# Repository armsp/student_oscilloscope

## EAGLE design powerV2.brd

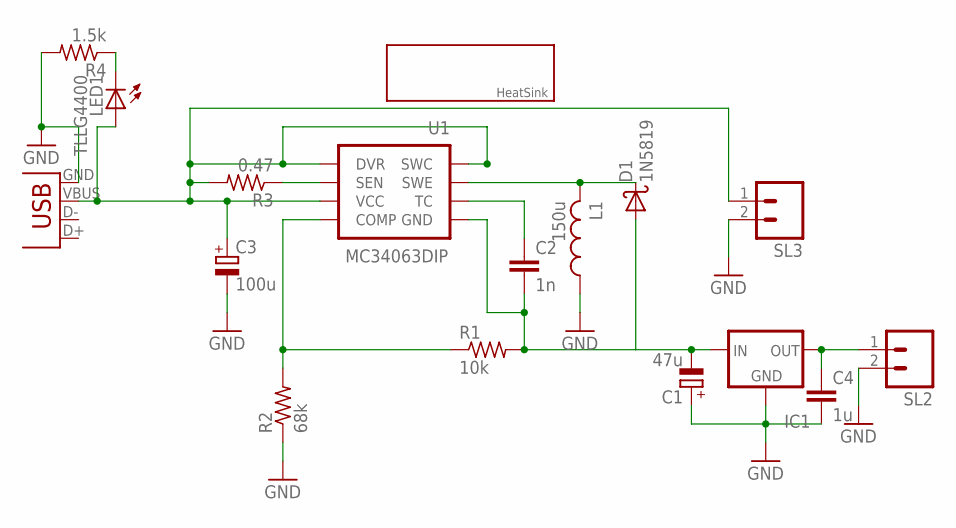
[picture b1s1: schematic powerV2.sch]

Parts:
C1: 47u; E2,5-7
C2: 1n; C025-024X044
C3: 100u; E2,5-7
C4: 1u; C025-024X044
D1: 1N5819; DO41-10
IC1: 79XXS
L1: 150u; 0204/7
LED1: TLLG4400; LED3MM
R1: 10k; 0204/7
R2: 68k; 0204/7
R3: 0.47; P0613/15
R4: 1.5k; 0204/7
SL2, SL3: M02; 02P
U1: MC34063DIP; DIP-08
U$1: HEATSINKMEDIUM; HEATSINK-MED
X1: USBSMD; USB-MINIB

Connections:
GND: C1.+, C3.-, C4.2, IC1.GND, L1.1, R2.1, R4.2, SL2.2, SL3.2, X1.GND
unnamed: R3.1, U1.7 (SEN)
unnamed: C3.+, LED1.A, R3.2, SL3.1, U1.1 (SWC), U1.6 (VCC), U1.8 (DVR), X1.VBUS
unnamed: C4.1, IC1.OUT, SL2.1
unnamed: C1.-, C2.2, D1.A, IC1.IN, R1.2, U1.4 (GND)
unnamed: R1.1, R2.2, U1.5 (COMP)
unnamed: D1.C, L1.2, U1.2 (SWE)
unnamed: C2.1, U1.3 (TC)
unnamed: LED1.K (C), R4.1

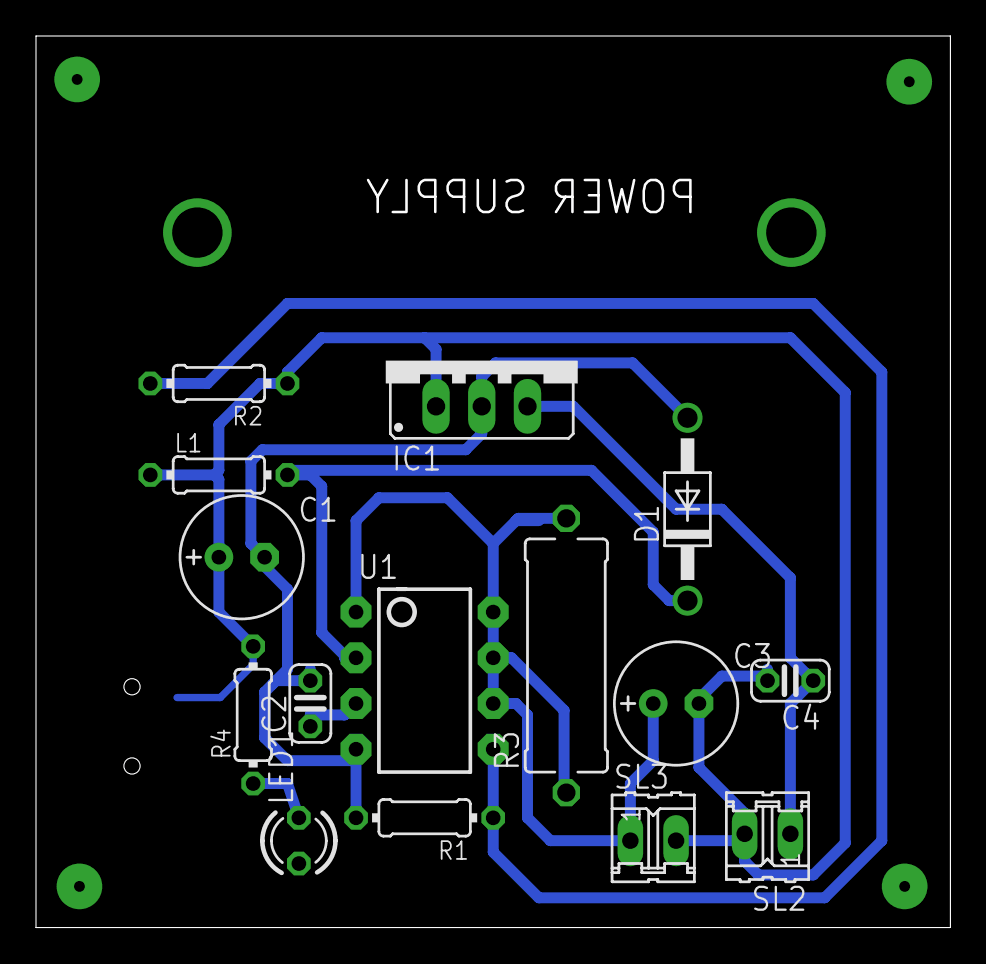
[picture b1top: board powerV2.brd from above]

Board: 2 copper layers, 50.8 x 49.5 mm, 17 parts (1 on the bottom side), 9 nets.

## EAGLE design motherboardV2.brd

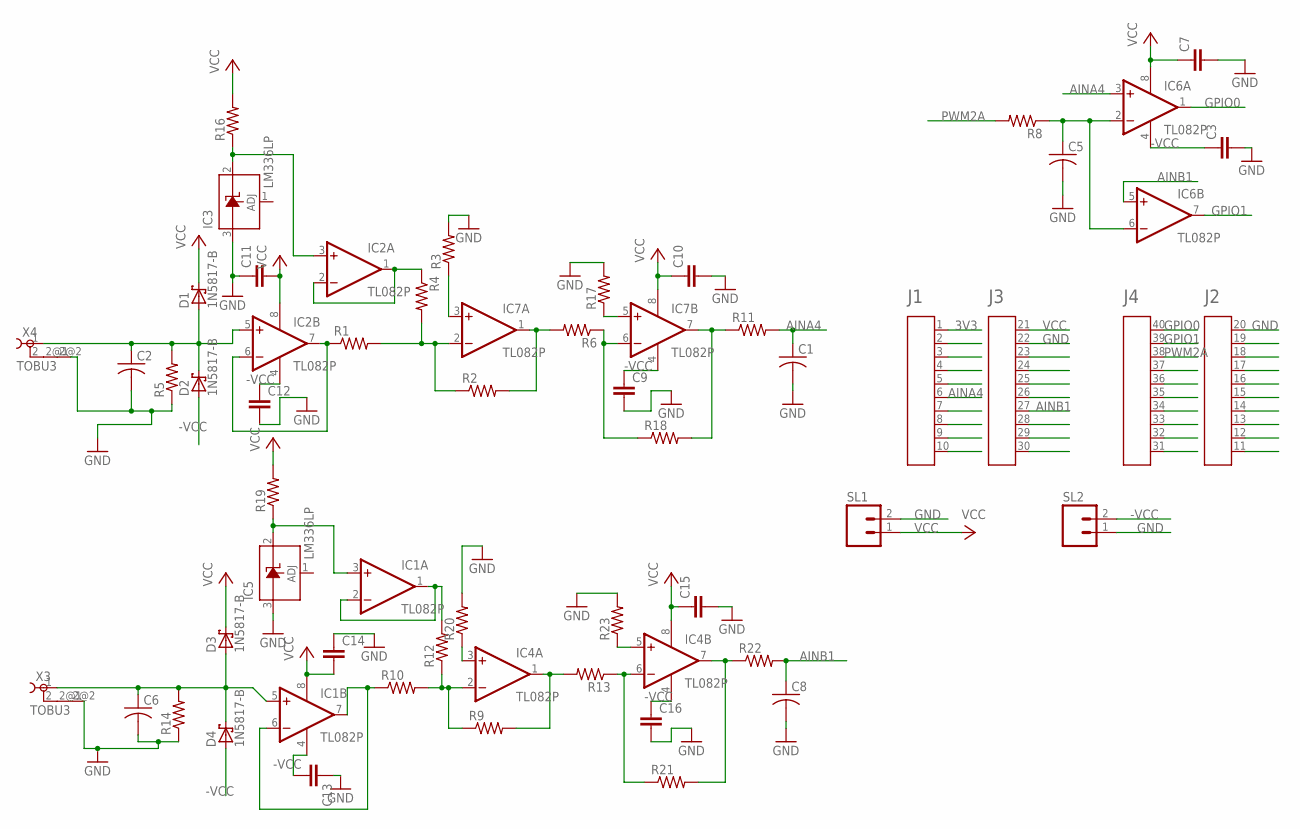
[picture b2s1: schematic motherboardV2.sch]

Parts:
A1: HEADER4X10-BOOSTERPACK; 4X10-BOOSTERPACK
C1, C2, C5, C6, C8: C-US025-025X050; C025-025X050
C3, C7, C9, C10, C11, C13, C14, C15, C16: C-EU025-025X050; C025-025X050
C12: C-EU025-030X050; C025-030X050
D1, D2, D3, D4: 1N5817-B; DO41-7.6
IC1, IC2, IC4, IC6, IC7: TL082P; DIL08
IC3, IC5: LM336LP; TO92
R1, R2, R3, R4, R5, R6, R8, R9, R10, R11, R12, R13, R14, R16, R17, R18, R19, R20, R21, R22, R23: R-US_0207/7; 0207/7
SL1, SL2: M02; 02P
X3, X4: TOBU3

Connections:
3V3: A1.1
-VCC: C3.1, C9.1, C12.1, C13.2, C16.1, D2.A, D4.A, IC1.4 (V-), IC2.4 (V-), IC4.4 (V-), IC6.4 (V-), IC7.4 (V-), SL2.2
AINA4: A1.6, C1.1, IC6.3 (+IN), R11.2
AINB1: A1.27, C8.1, IC6.5 (+IN), R22.2
GND: A1.20, A1.22, C1.2, C2.2, C3.2, C5.2, C6.2, C7.2, C8.2, C9.2, C10.2, C11.1, C12.2, C13.1, C14.1, C15.2, C16.2, IC3.3 (A), IC5.3 (A), R3.2, R5.1, R14.1, R17.2, R20.2, R23.2, SL1.2, SL2.1, X3.2@2 (4), X4.2@2 (4)
GPIO0: A1.40, IC6.1 (OUT)
GPIO1: A1.39, IC6.7 (OUT)
unnamed: IC2.3 (+IN), IC3.2 (C), R16.1
unnamed: IC7.2 (-IN), R1.2, R2.1, R4.2
unnamed: C6.1, D3.A, D4.C, IC1.5 (+IN), R14.2, X3.1
unnamed: IC7.1 (OUT), R2.2, R6.2
unnamed: IC7.3 (+IN), R3.1
unnamed: IC1.3 (+IN), IC5.2 (C), R19.1
unnamed: C5.1, IC6.2 (-IN), IC6.6 (-IN), R8.1
unnamed: IC2.1 (OUT), IC2.2 (-IN), R4.1
unnamed: IC7.6 (-IN), R6.1, R18.1
unnamed: IC4.2 (-IN), R9.1, R10.2, R12.1
unnamed: IC1.1 (OUT), IC1.2 (-IN), R12.2
unnamed: IC7.5 (+IN), R17.1
unnamed: C2.1, D1.A, D2.C, IC2.5 (+IN), R5.2, X4.1
unnamed: IC4.1 (OUT), R9.2, R13.2
unnamed: IC7.7 (OUT), R11.1, R18.2
unnamed: IC4.3 (+IN), R20.1
unnamed: IC4.7 (OUT), R21.2, R22.1
unnamed: IC4.6 (-IN), R13.1, R21.1
unnamed: IC4.5 (+IN), R23.1
unnamed: IC1.6 (-IN), IC1.7 (OUT), R10.1
unnamed: IC2.6 (-IN), IC2.7 (OUT), R1.1
PWM2A: A1.38, R8.2
VCC: A1.21, C7.1, C10.1, C11.2, C14.2, C15.1, D1.C, D3.C, IC1.8 (V+), IC2.8 (V+), IC4.8 (V+), IC6.8 (V+), IC7.8 (V+), R16.2, R19.2, SL1.1

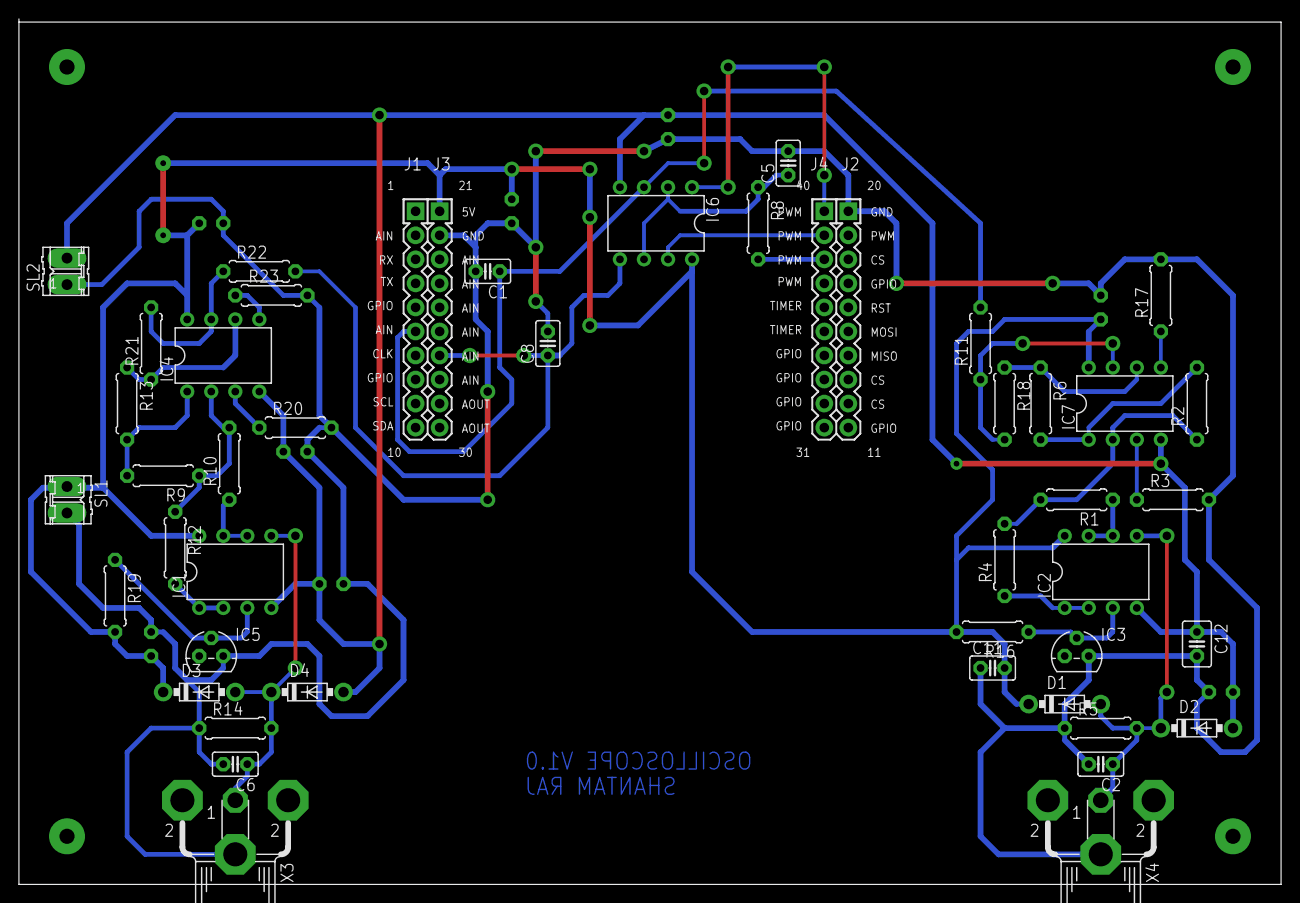
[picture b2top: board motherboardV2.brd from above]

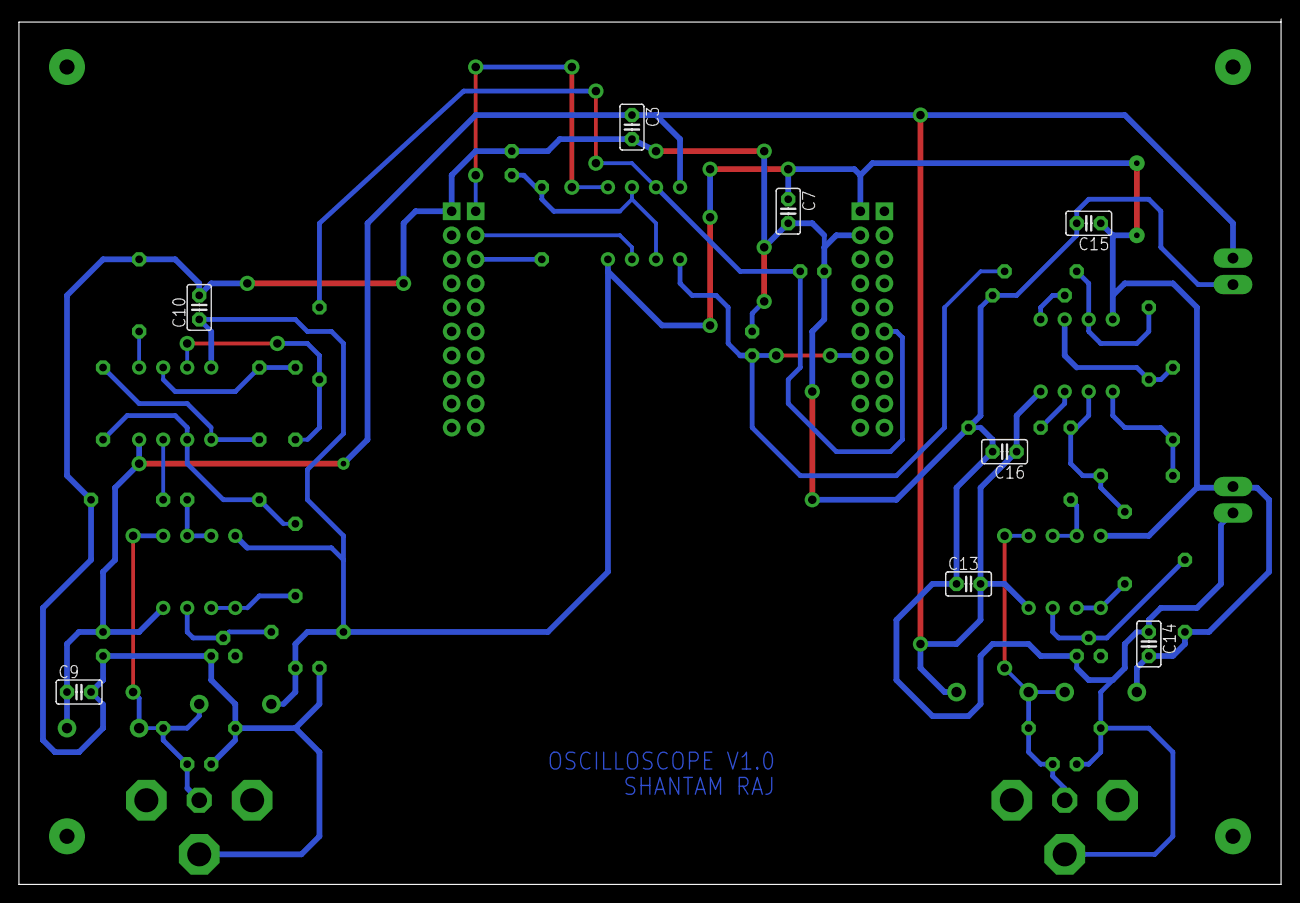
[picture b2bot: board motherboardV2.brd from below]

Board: 2 copper layers, 133.3 x 91.4 mm, 52 parts (8 on the bottom side), 29 nets.

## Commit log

2015-07-31 power source files added

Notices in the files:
parts and their libraries:
SparkFun-PowerIC: Licensing: Creative Commons ShareAlike 4.0 International - https://creativecommons.org/licenses/by-sa/4.0
